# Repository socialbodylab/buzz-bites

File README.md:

# buzz-bites

Experimental vibe motor modules for building haptic projects.

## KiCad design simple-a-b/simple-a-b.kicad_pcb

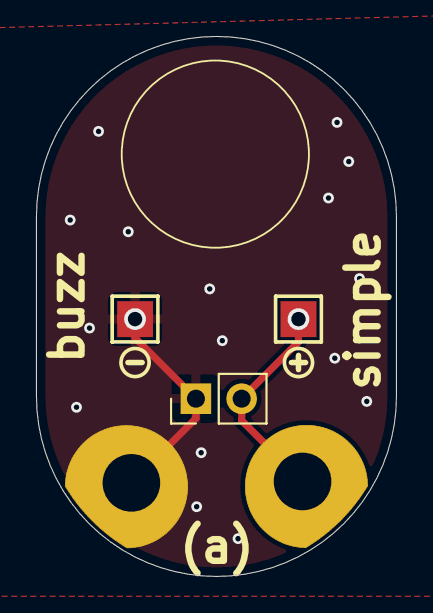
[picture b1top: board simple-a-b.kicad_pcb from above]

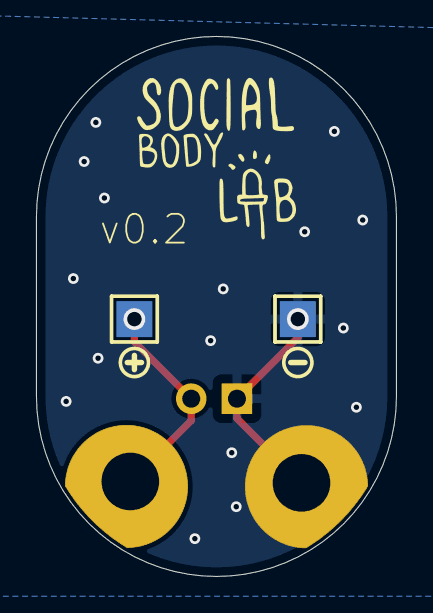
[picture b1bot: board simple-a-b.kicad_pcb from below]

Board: 2 copper layers, 20.0 x 30.0 mm, 11 parts (4 on the bottom side), 2 nets.

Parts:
H1, H2: MountingHole_Pad; edge_tiny
J1: Conn_01x02_Pin; PinHeader_1x02_P2.54mm_Vertical
J2, J3: TESTPOINT_PAD_2MM
TP3, TP4: TESTPOINT_PAD_2MM
U$2, U$2#2: SYMBOL_PLUS
U$3, U$3#2: SYMBOL_MINUS

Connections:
GND: H2.1, J1.1, J3.Pin_1, TP4.Pin_1
unnamed: H1.1, J1.2, J2.Pin_2, TP3.1

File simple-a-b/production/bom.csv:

Designator,Footprint,Quantity,Value,LCSC Part #
"H1, H2",edge_tiny,2,MountingHole_Pad,
J1,PinHeader_1x02_P2.54mm_Vertical,1,Conn_01x02_Pin,
"J2, J3, TP3, TP4",TESTPOINT_PAD_2MM,4,,
"JP1, JP3",1X01_OVAL,2,,
"U$2_3, U$2_2, U$2",SYMBOL_PLUS,3,,
"U$3_3, U$3_2, U$3",SYMBOL_MINUS,3,,
